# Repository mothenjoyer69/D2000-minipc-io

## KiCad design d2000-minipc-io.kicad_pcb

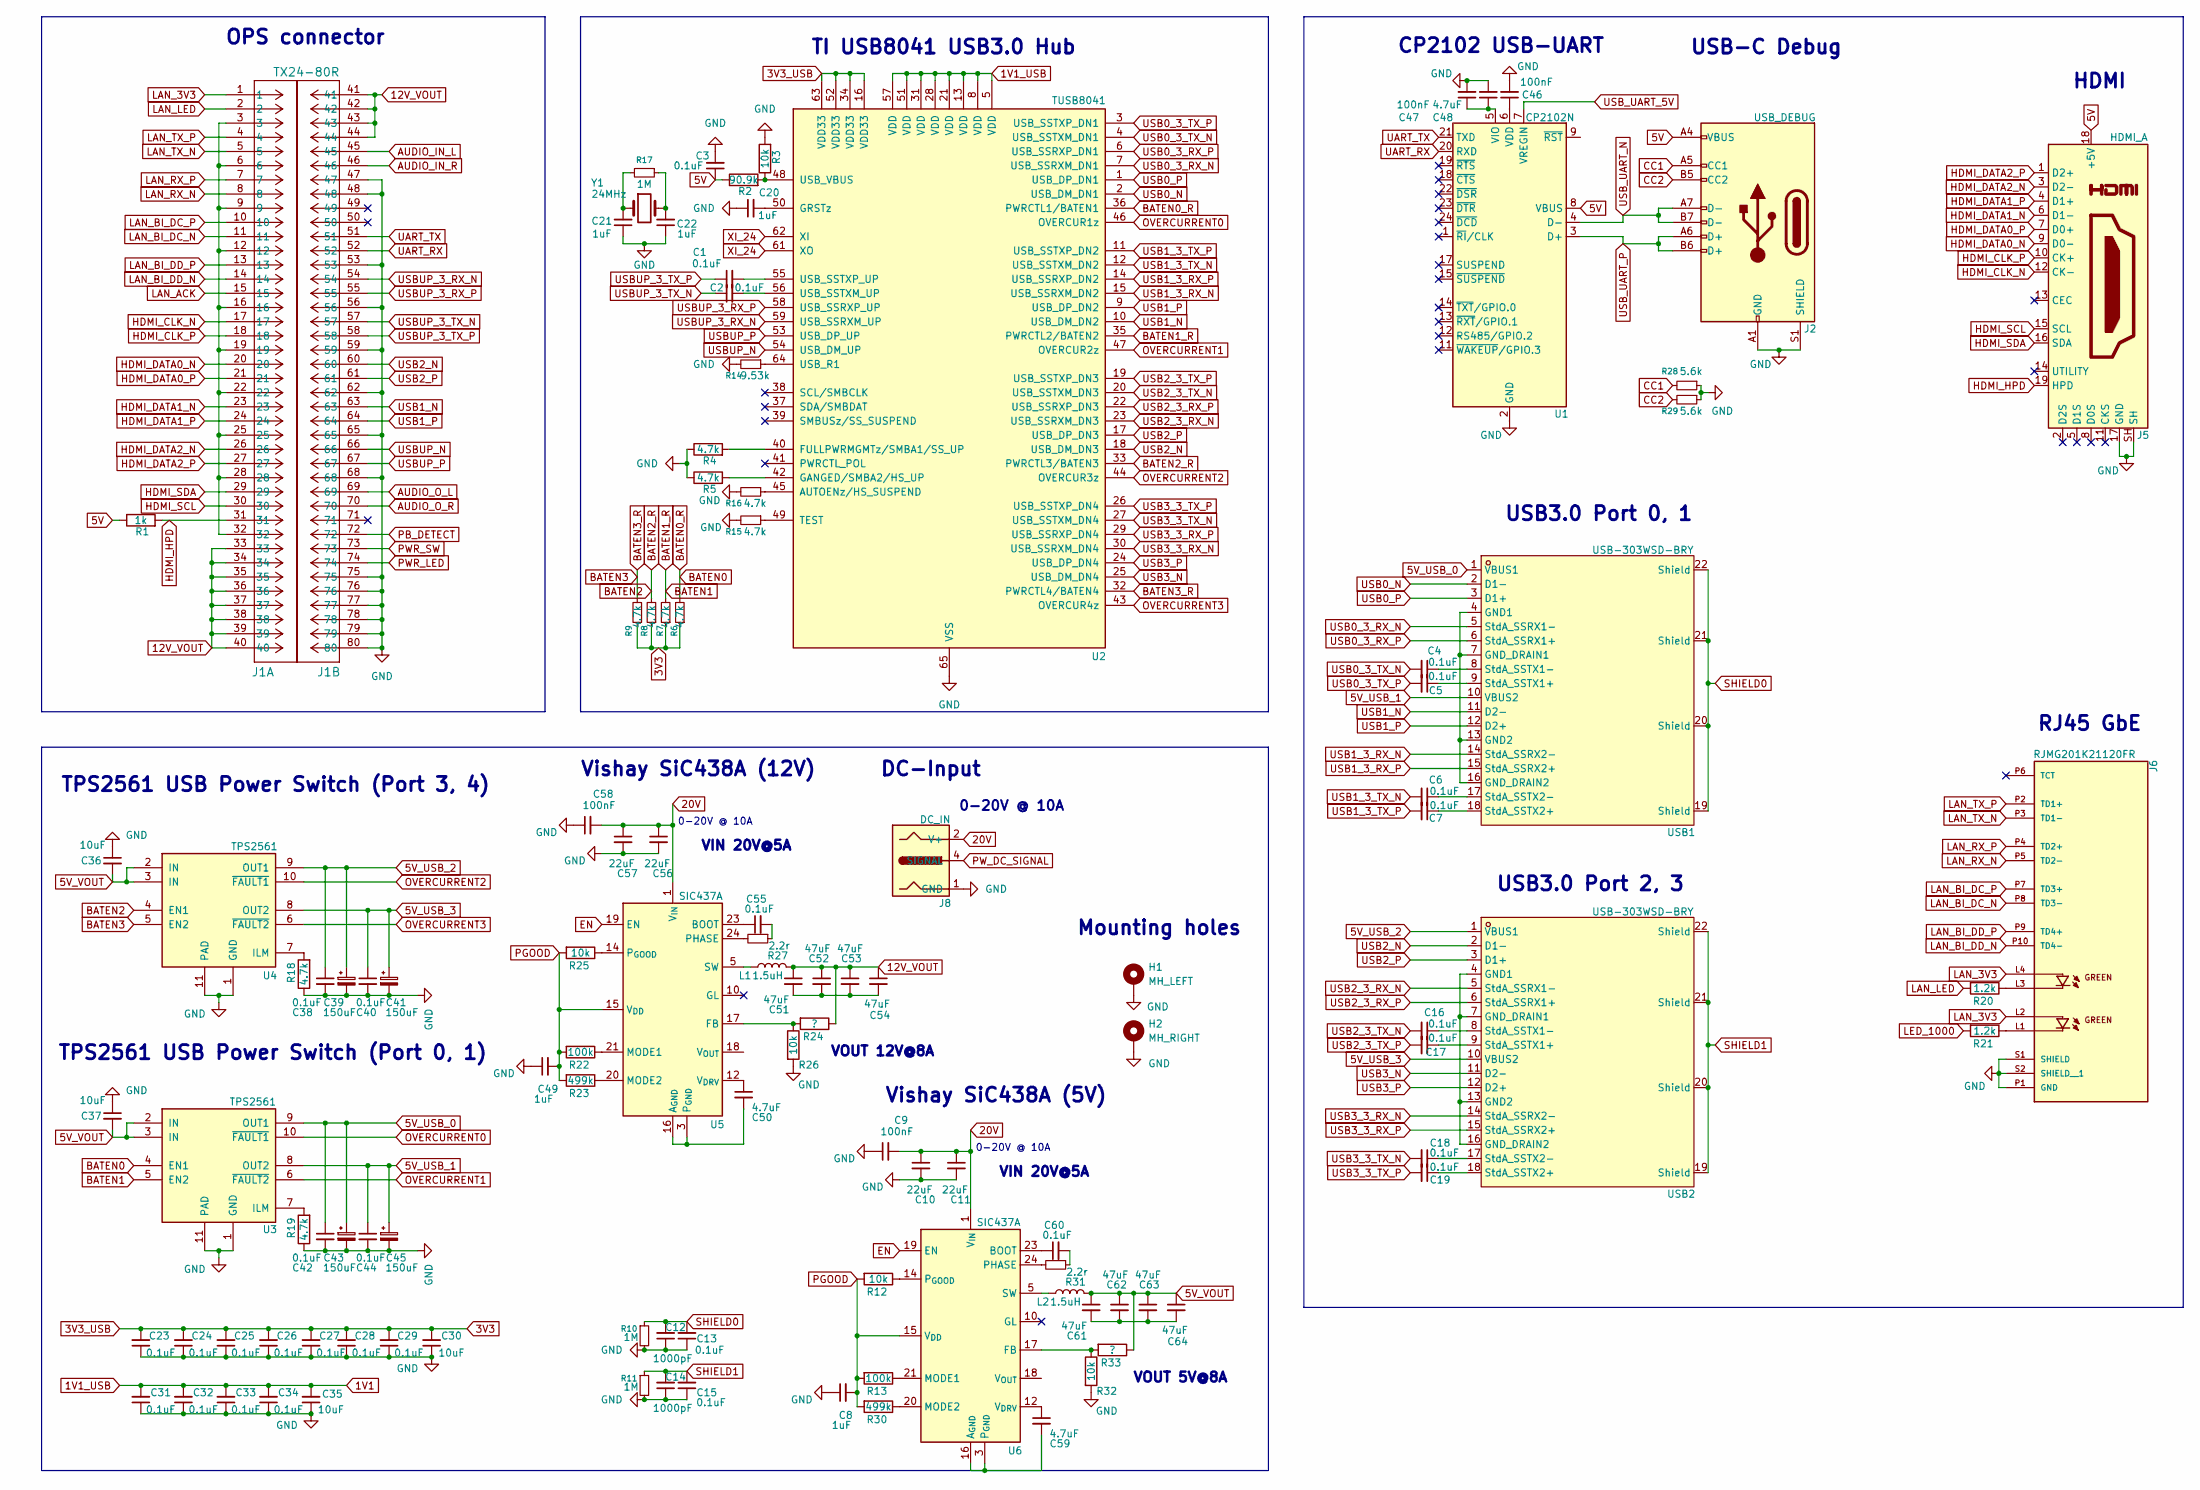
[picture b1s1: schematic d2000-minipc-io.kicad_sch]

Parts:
C1, C2, C3, C4, C5, C6, C7, C13, C15, C16, C17, C18, C19, C23, C24, C25, C26, C27, C28, C29, C31, C32, C33, C34, C38, C40, C42, C44: 0.1uF; C_0402_1005Metric
C8, C49: 1uF; C_0603_1608Metric
C9, C58: 100nF; C_0603_1608Metric
C10, C11, C56, C57: 22uF; C_0603_1608Metric
C12, C14: 1000pF; C_0402_1005Metric
C20, C21, C22: 1uF; C_0402_1005Metric
C30, C35, C36, C37: 10uF; C_0603_1608Metric
C39, C41, C43, C45: 150uF; C_Elec_4x5.4
C46, C47: 100nF; C_0402_1005Metric
C48, C50, C59: 4.7uF; C_0603_1608Metric
C51, C52, C53, C54, C61, C62, C63, C64: 47uF; C_0603_1608Metric
C55, C60: 0.1uF; C_0603_1608Metric
H1: MH_LEFT; MountingHole_3.2mm_M3_DIN965_Pad
H2: MH_RIGHT; MountingHole_3.2mm_M3_DIN965_Pad
J1: TX24-80R; CON80_2X40_MU_TX24_JAE
J2: USB_DEBUG; USB_C_Receptacle_HRO_TYPE-C-31-M-12
J5: HDMI_A; HDMI_A_Molex_208658-1001_Horizontal
J6: RJMG201K21120FR; AMPHENOL_RJMG201K21120FR; PARTREV AX2
J8: DC_IN; DC-505
L1, L2: 1.5uH; L_TDK_VLP8040
R1: 1k; R_0402_1005Metric
R2: 90.9k; R_0402_1005Metric
R3: 10k; R_0402_1005Metric
R4, R5, R6, R7, R8, R9, R15, R16, R18, R19: 4.7k; R_0402_1005Metric
R10, R11, R17: 1M; R_0402_1005Metric
R12, R25, R26, R32: 10k; R_0603_1608Metric
R13, R22: 100k; R_0603_1608Metric
R14: 9.53k; R_0402_1005Metric
R20, R21: 1.2k; R_0402_1005Metric
R23, R30: 499k; R_0603_1608Metric
R24, R33: ?; R_0603_1608Metric
R27, R31: 2.2r; R_0603_1608Metric
R28, R29: 5.6k; R_0402_1005Metric
U1: CP2102N; QFN-24-1EP_4x4mm_P0.5mm_EP2.6x2.6mm
U2: TUSB8041; QFN-64-1EP_9x9mm_P0.5mm_EP6x6mm_ThermalVias
U3, U4: TPS2561; VSON-10-1EP_3x3mm_P0.5mm_EP1.65x2.4mm_ThermalVias
U5, U6: SIC437A; Vishay_PowerPAK_MLP44-24L_ThermalVias
USB1, USB2: USB-303WSD-BRY; USB-A-TH_XUNPU_USB-303WSD-BRY; LCSC Part C2895028
Y1: 24MHz; Crystal_SMD_Abracon_ABM3B-4Pin_5.0x3.2mm

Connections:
1V1: C31.2, C32.2, C33.2, C34.2, C35.2, U2.5 (VDD), U2.8 (VDD), U2.13 (VDD), U2.21 (VDD), U2.28 (VDD), U2.31 (VDD), U2.51 (VDD), U2.57 (VDD)
3V3: C23.2, C24.2, C25.2, C26.2, C27.2, C28.2, C29.2, C30.2, R6.1, R7.1, R8.1, R9.1, U2.16 (VDD33), U2.34 (VDD33), U2.52 (VDD33), U2.63 (VDD33)
5V: C3.1, J2.A4 (VBUS), J2.A9 (VBUS), J2.B4 (VBUS), J2.B9 (VBUS), J5.18 (+5V), R1.1, R2.1, U1.8 (VBUS)
5V_USB_0: C42.1, C43.1, U3.9 (OUT1), USB1.1 (VBUS1)
5V_USB_1: C44.1, C45.1, U3.8 (OUT2), USB1.10 (VBUS2)
5V_USB_2: C38.1, C39.1, U4.9 (OUT1), USB2.1 (VBUS1)
5V_USB_3: C40.1, C41.1, U4.8 (OUT2), USB2.10 (VBUS2)
5V_VOUT: C36.2, C37.2, C61.1, C62.1, C63.1, C64.1, L2.2, R33.1, U3.2 (IN), U3.3 (IN), U4.2 (IN), U4.3 (IN)
12V_VOUT: C51.1, C52.1, C53.1, C54.1, J1.33, J1.34, J1.35, J1.36, J1.37, J1.38, J1.39, J1.40, J1.41, J1.42, J1.43, J1.44, L1.2, R24.1
20V: C9.2, C10.1, C11.1, C56.1, C57.1, C58.2, J8.2 (V+), U5.1 (V_{IN}), U5.2 (V_{IN}), U5.22 (V_{IN}), U5.26 (V_{IN}), U6.1 (V_{IN}), U6.2 (V_{IN}), U6.22 (V_{IN}), U6.26 (V_{IN}); also elsewhere on the board
AUDIO_IN_L: J1.45
AUDIO_IN_R: J1.46
AUDIO_O_L: J1.69
AUDIO_O_R: J1.70
BATEN0: R6.2, U2.36 (PWRCTL1/BATEN1), U3.4 (EN1)
BATEN1: R7.2, U2.35 (PWRCTL2/BATEN2), U3.5 (EN2)
BATEN2: R8.2, U2.33 (PWRCTL3/BATEN3), U4.4 (EN1)
BATEN3: R9.2, U2.32 (PWRCTL4/BATEN4), U4.5 (EN2)
CC1: J2.A5 (CC1), R28.2
CC2: J2.B5 (CC2), R29.2
EN: U5.19 (EN), U6.19 (EN)
GND: C3.2, C8.1, C9.1, C10.2, C11.2, C12.1, C13.1, C14.1, C15.1, C20.1, C21.1, C22.1, C23.1, C24.1, C25.1, C26.1, C27.1, C28.1, C29.1, C30.1, C31.1, C32.1, C33.1, C34.1, C35.1, C36.1, C37.1, C38.2, C39.2, C40.2, C41.2, C42.2, C43.2, C44.2, C45.2, C46.2, C47.2, C48.2, C49.1, C56.2, C57.2, C58.1, H1.1, H2.1, J1.47, J1.48, J1.53, J1.56, J1.59, J1.62, J1.65, J1.68, J1.75, J1.76, J1.77, J1.78, J1.79, J1.80, J2.A1 (GND), J2.A12 (GND), J2.B1 (GND), J2.B12 (GND), J2.S1 (SHIELD), J5.17 (GND), J5.SH, J6.P1 (GND), J6.S1 (SHIELD), J6.S2 (SHIELD__1), J8.1 (GND), R3.2, R4.1, R5.1, R10.2, R11.2, R14.2, R15.2, R16.2, R18.1, R19.1, R26.2, R28.1, R29.1, R32.2, U1.2 (GND), U1.25 (GND), U2.65 (VSS), U3.1 (GND), U3.11 (PAD), U4.1 (GND), U4.11 (PAD)
HDMI_CLK_N: J1.17, J5.12 (CK-)
HDMI_CLK_P: J1.18, J5.10 (CK+)
HDMI_DATA0_N: J1.20, J5.9 (D0-)
HDMI_DATA0_R: J1.21, J5.7 (D0+)
HDMI_DATA1_N: J1.23, J5.6 (D1-)
HDMI_DATA1_P: J1.24, J5.4 (D1+)
HDMI_DATA2_N: J1.26, J5.3 (D2-)
HDMI_DATA2_P: J1.27, J5.1 (D2+)
HDMI_HPD: J1.31, J5.19 (HPD), R1.2
HDMI_SCL: J1.30, J5.15 (SCL)
HDMI_SDA: J1.29, J5.16 (SDA)
LAN_3V3: J1.1, J6.L2, J6.L4
LAN_ACK: J1.15
LAN_BI_DC_N: J1.11, J6.P8 (TD3-)
LAN_BI_DC_P: J1.10, J6.P7 (TD3+)
LAN_BI_DD_N: J1.14, J6.P10 (TD4-)
LAN_BI_DD_P: J1.13, J6.P9 (TD4+)
LAN_LED: J1.2, R20.2
LAN_RX_N: J1.8, J6.P5 (TD2-)
LAN_RX_P: J1.7, J6.P4 (TD2+)
LAN_TX_N: J1.5, J6.P3 (TD1-)
LAN_TX_P: J1.4, J6.P2 (TD1+)
LED_1000: R21.2
unnamed: C21.2, R17.2, Y1.1
unnamed: C22.2, R17.1, Y1.2
unnamed: C50.2, U5.3 (P_{GND}), U5.4 (P_{GND}), U5.13 (P_{GND}), U5.16 (A_{GND}), U5.25 (A_{GND}), U5.27 (P_{GND})
unnamed: C51.2, C52.2, C53.2, C54.2
unnamed: C55.2, R27.1
unnamed: C59.2, U6.3 (P_{GND}), U6.4 (P_{GND}), U6.13 (P_{GND}), U6.16 (A_{GND}), U6.25 (A_{GND}), U6.27 (P_{GND})
unnamed: C60.2, R31.1
unnamed: C61.2, C62.2, C63.2, C64.2
unnamed: J1.3, J1.6, J1.9, J1.12, J1.16, J1.19, J1.22, J1.25, J1.28, J1.32
unnamed: J6.L1, R21.1
unnamed: J6.L3, R20.1
unnamed: L1.1, U5.5 (SW), U5.6 (SW), U5.7 (SW), U5.8 (SW), U5.9 (SW)
unnamed: L2.1, U6.5 (SW), U6.6 (SW), U6.7 (SW), U6.8 (SW), U6.9 (SW)
unnamed: C46.1, U1.6 (VDD)
unnamed: C47.1, C48.1, U1.5 (VIO)
unnamed: R16.1, U2.45 (AUTOENz/HS_SUSPEND)
unnamed: R4.2, U2.40 (FULLPWRMGMTz/SMBA1/SS_UP)
unnamed: R5.2, U2.42 (GANGED/SMBA2/HS_UP)
unnamed: C20.2, U2.50 (GRSTz)
unnamed: R15.1, U2.49 (TEST)
unnamed: R14.1, U2.64 (USB_R1)
unnamed: C2.2, U2.56 (USB_SSTXM_UP)
unnamed: C1.2, U2.55 (USB_SSTXP_UP)
unnamed: R2.2, R3.1, U2.48 (USB_VBUS)
unnamed: R19.2, U3.7 (ILM)
unnamed: R18.2, U4.7 (ILM)
unnamed: C55.1, U5.23 (BOOT)
unnamed: R24.2, R26.1, U5.17 (FB)
unnamed: R22.1, U5.21 (MODE1)
unnamed: R23.1, U5.20 (MODE2)
unnamed: R27.2, U5.24 (PHASE)
unnamed: R25.1, U5.14 (P_{GOOD})
unnamed: C50.1, U5.12 (V_{DRV})
unnamed: C60.1, U6.23 (BOOT)
unnamed: R32.1, R33.2, U6.17 (FB)
unnamed: R13.1, U6.21 (MODE1)
unnamed: R30.1, U6.20 (MODE2)
unnamed: R31.2, U6.24 (PHASE)
unnamed: R12.1, U6.14 (P_{GOOD})
unnamed: C59.1, U6.12 (V_{DRV})
unnamed: USB1.4 (GND1), USB1.7 (GND_DRAIN1), USB1.13 (GND2), USB1.16 (GND_DRAIN2)
unnamed: C5.1, USB1.9 (StdA_SSTX1+)
unnamed: C4.1, USB1.8 (StdA_SSTX1-)
unnamed: C7.1, USB1.18 (StdA_SSTX2+)
unnamed: C6.1, USB1.17 (StdA_SSTX2-)
unnamed: USB2.4 (GND1), USB2.7 (GND_DRAIN1), USB2.13 (GND2), USB2.16 (GND_DRAIN2)
unnamed: C17.1, USB2.9 (StdA_SSTX1+)
unnamed: C16.1, USB2.8 (StdA_SSTX1-)
unnamed: C19.1, USB2.18 (StdA_SSTX2+)
unnamed: C18.1, USB2.17 (StdA_SSTX2-)
OVERCURRENT0: U2.46 (OVERCUR1z), U3.10 (~FAULT1)
OVERCURRENT1: U2.47 (OVERCUR2z), U3.6 (~FAULT2)
OVERCURRENT2: U2.44 (OVERCUR3z), U4.10 (~FAULT1)
OVERCURRENT3: U2.43 (OVERCUR4z), U4.6 (~FAULT2)
PB_DETECT: J1.72
PGOOD: C8.2, C49.2, R12.2, R13.2, R22.2, R23.2, R25.2, R30.2, U5.15 (V_{DD}), U6.15 (V_{DD})
PWR_LED: J1.74
PWR_SW: J1.73
PW_DC_SIGNAL: J8.4 (SIGNAL)
SHIELD0: C12.2, C13.2, R10.1, USB1.19 (Shield), USB1.20 (Shield), USB1.21 (Shield), USB1.22 (Shield)
SHIELD1: C14.2, C15.2, R11.1, USB2.19 (Shield), USB2.20 (Shield), USB2.21 (Shield), USB2.22 (Shield)
UART_RX: J1.52, U1.20 (RXD)
UART_TX: J1.51, U1.21 (TXD)
USB0_3_RX_N: U2.7 (USB_SSRXM_DN1), USB1.5 (StdA_SSRX1-)
USB0_3_RX_P: U2.6 (USB_SSRXP_DN1), USB1.6 (StdA_SSRX1+)
USB0_3_TX_N: C4.2, U2.4 (USB_SSTXM_DN1)
USB0_3_TX_P: C5.2, U2.3 (USB_SSTXP_DN1)
USB0_N: U2.2 (USB_DM_DN1), USB1.2 (D1-)
USB0_P: U2.1 (USB_DP_DN1), USB1.3 (D1+)
USB1_3_RX_N: U2.15 (USB_SSRXM_DN2), USB1.14 (StdA_SSRX2-)
USB1_3_RX_P: U2.14 (USB_SSRXP_DN2), USB1.15 (StdA_SSRX2+)
USB1_3_TX_N: C6.2, U2.12 (USB_SSTXM_DN2)
USB1_3_TX_P: C7.2, U2.11 (USB_SSTXP_DN2)
USB1_N: J1.63, U2.10 (USB_DM_DN2), USB1.11 (D2-)
USB1_P: J1.64, U2.9 (USB_DP_DN2), USB1.12 (D2+)
USB2_3_RX_N: U2.23 (USB_SSRXM_DN3), USB2.5 (StdA_SSRX1-)
USB2_3_RX_P: U2.22 (USB_SSRXP_DN3), USB2.6 (StdA_SSRX1+)
USB2_3_TX_N: C16.2, U2.20 (USB_SSTXM_DN3)
USB2_3_TX_P: C17.2, U2.19 (USB_SSTXP_DN3)
USB2_N: J1.60, U2.18 (USB_DM_DN3), USB2.2 (D1-)
USB2_P: J1.61, U2.17 (USB_DP_DN3), USB2.3 (D1+)
USB3_3_RX_N: U2.30 (USB_SSRXM_DN4), USB2.14 (StdA_SSRX2-)
USB3_3_RX_P: U2.29 (USB_SSRXP_DN4), USB2.15 (StdA_SSRX2+)
USB3_3_TX_N: C18.2, U2.27 (USB_SSTXM_DN4)
USB3_3_TX_P: C19.2, U2.26 (USB_SSTXP_DN4)
USB3_N: U2.25 (USB_DM_DN4), USB2.11 (D2-)
USB3_P: U2.24 (USB_DP_DN4), USB2.12 (D2+)
USBUP_3_RX_N: J1.54, U2.59 (USB_SSRXM_UP)
USBUP_3_RX_P: J1.55, U2.58 (USB_SSRXP_UP)
USBUP_3_TX_N: C2.1, J1.57
USBUP_3_TX_P: C1.1, J1.58
USBUP_N: J1.66, U2.54 (USB_DM_UP)
USBUP_P: J1.67, U2.53 (USB_DP_UP)
USB_UART_5V: U1.7 (VREGIN)
USB_UART_N: J2.A7 (D-), J2.B7 (D-), U1.4 (D-)
USB_UART_P: J2.A6 (D+), J2.B6 (D+), U1.3 (D+)
XI_24: U2.61 (XO), U2.62 (XI)

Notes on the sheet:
USB3.0 Port 0, 1
0-20V @ 10A
USB-C Debug
Vishay SiC438A (5V)
VOUT 5V@8A
VIN 20V@5A
Vishay SiC438A (12V)
CP2102 USB-UART
RJ45 GbE
TI USB8041 USB3.0 Hub
Mounting holes
USB3.0 Port 2, 3
OPS connector
TPS2561 USB Power Switch (Port 0, 1)
HDMI
VOUT 12V@8A
DC-Input
TPS2561 USB Power Switch (Port 3, 4)

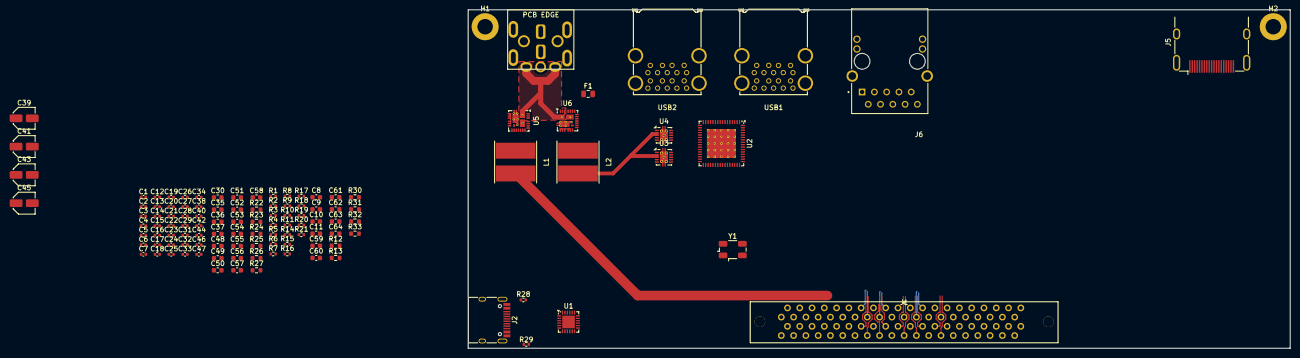
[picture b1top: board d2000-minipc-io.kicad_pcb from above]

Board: 2 copper layers, 170.0 x 70.0 mm, 116 parts (0 on the bottom side), 131 nets.

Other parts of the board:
F1: Fuse; Fuse_0805_2012Metric

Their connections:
20V: F1.1; also elsewhere on the board

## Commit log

2025-08-09 add initial files
2025-08-10 updated schematic
